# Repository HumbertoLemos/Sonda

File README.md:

# Sonda
Projeto da sonda para ensaios em aeronaves

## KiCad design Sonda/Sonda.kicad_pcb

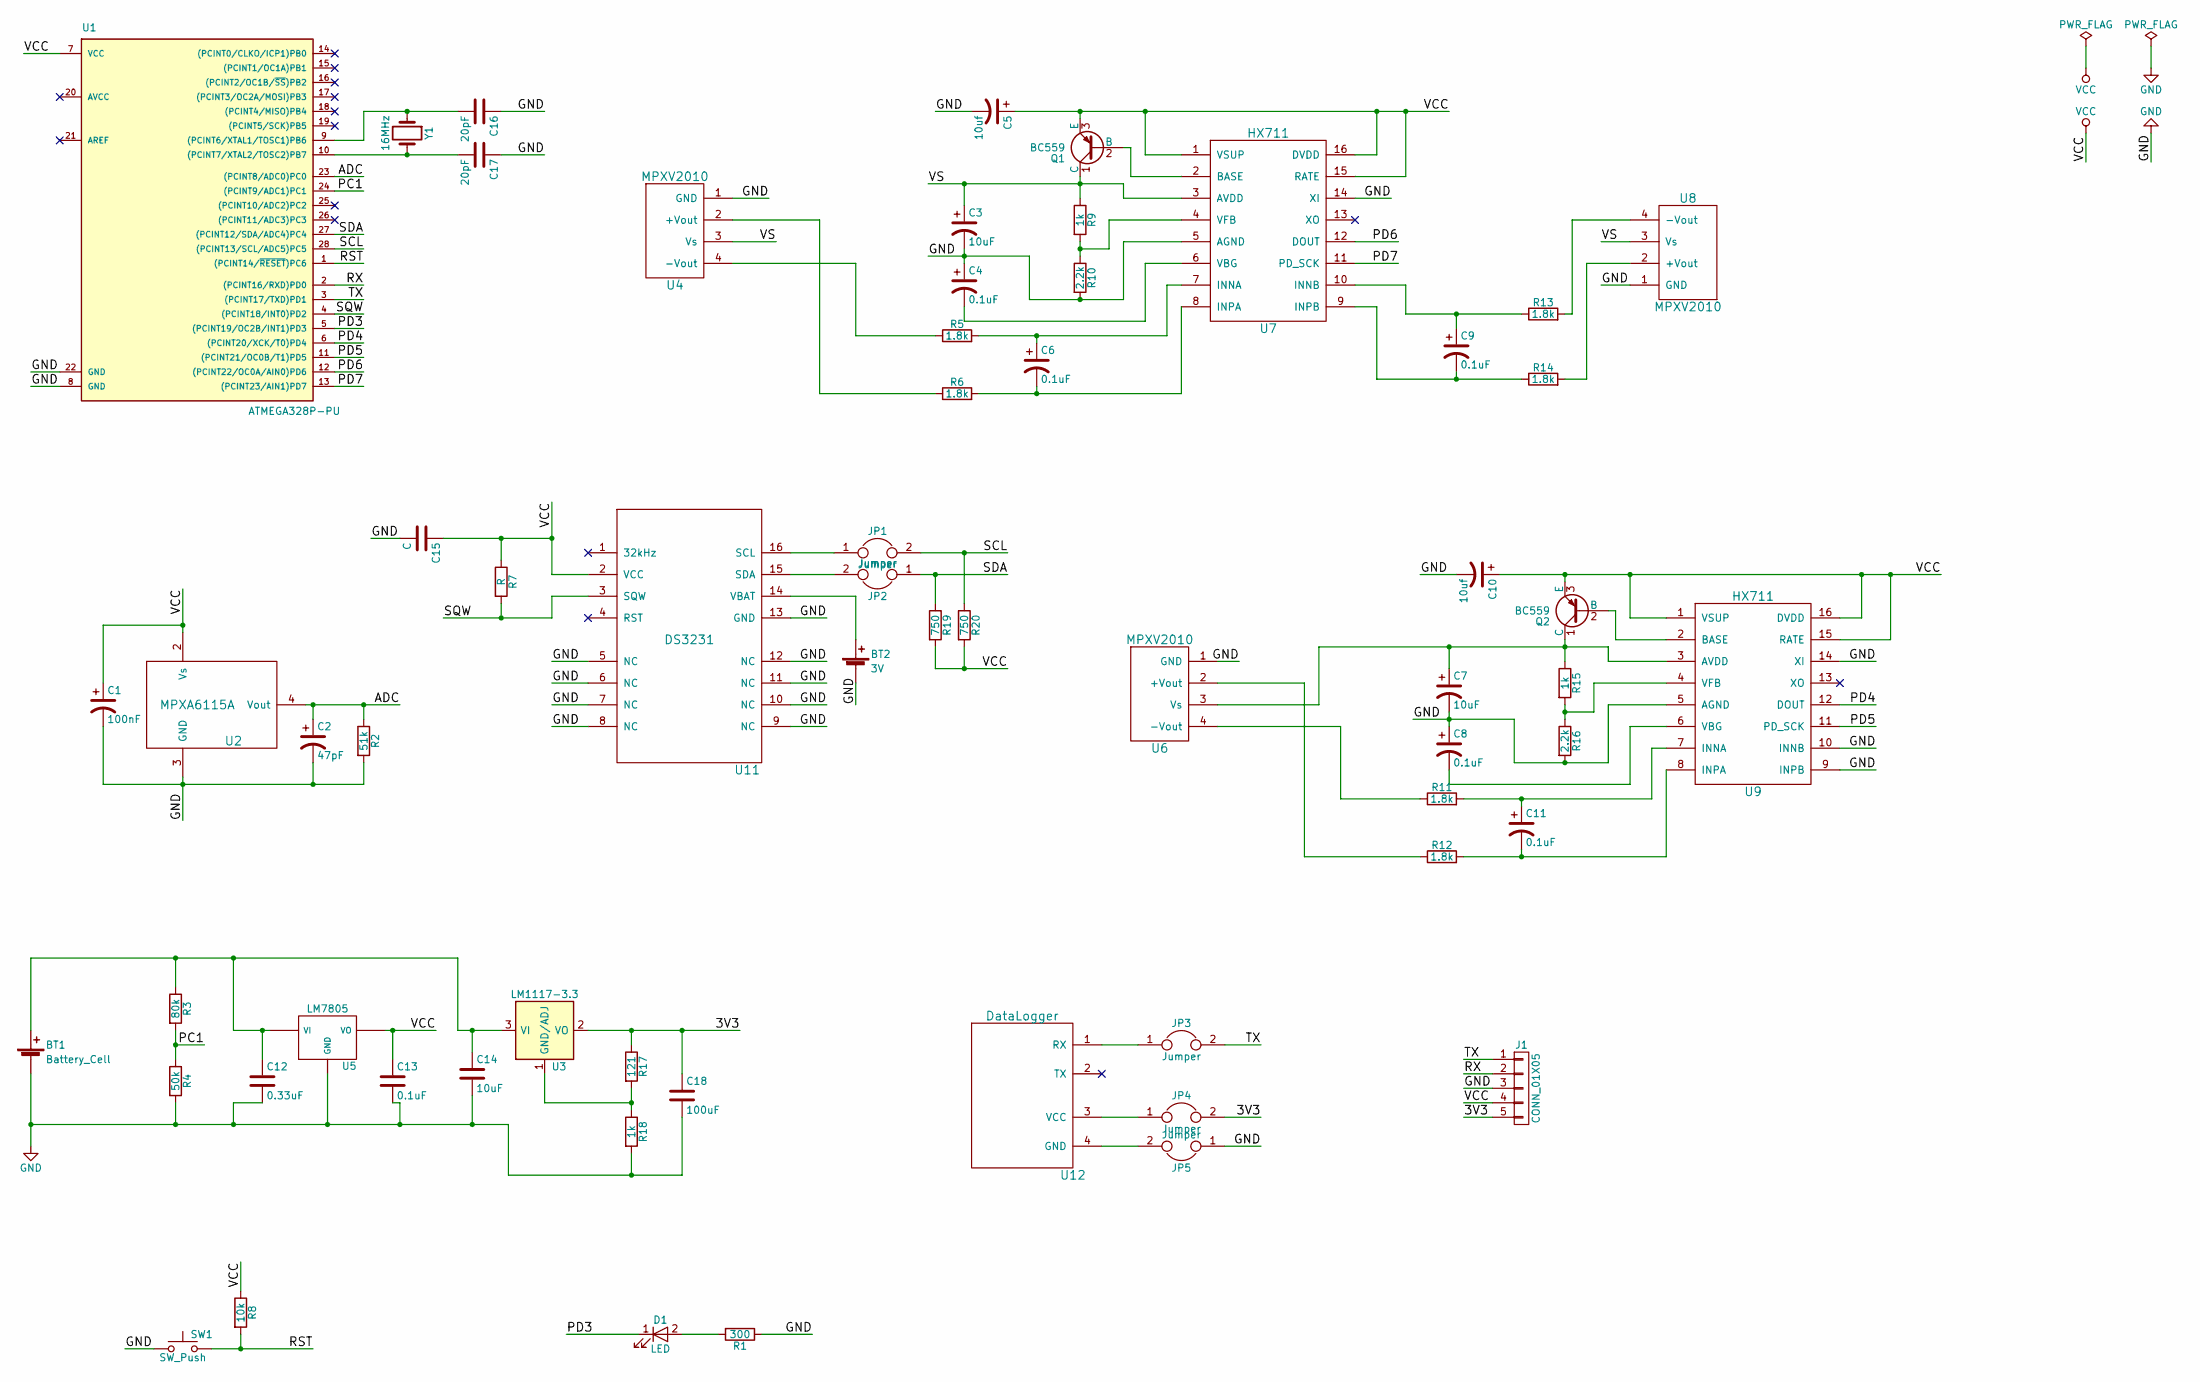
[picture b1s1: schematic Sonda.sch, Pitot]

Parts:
BT1: Battery_Cell; Pin_Header_Straight_1x02_Pitch2.54mm
BT2: 3V; SuporteBateria
C1: 100nF; C_Disc_D4.3mm_W1.9mm_P5.00mm
C2: 47pF; C_Disc_D4.3mm_W1.9mm_P5.00mm
C3, C7, C14: 10uF; C_Disc_D4.3mm_W1.9mm_P5.00mm
C4, C6, C8, C9, C11, C13: 0.1uF; C_Disc_D4.3mm_W1.9mm_P5.00mm
C5, C10: 10uf; C_Disc_D4.3mm_W1.9mm_P5.00mm
C12: 0.33uF; C_Disc_D4.3mm_W1.9mm_P5.00mm
C15: C; C_Disc_D4.3mm_W1.9mm_P5.00mm
C16, C17: 20pF; C_Disc_D4.3mm_W1.9mm_P5.00mm
C18: 100uF; C_Disc_D4.3mm_W1.9mm_P5.00mm
D1: LED; LED_D3.0mm
J1: CONN_01X05; Pin_Header_Straight_1x05_Pitch2.54mm
JP1, JP2, JP3, JP4, JP5: Jumper; Pin_Header_Straight_1x02_Pitch2.54mm
Q1, Q2: BC559; TO-92_Molded_Narrow
R1: 300; R_Axial_DIN0207_L6.3mm_D2.5mm_P10.16mm_Horizontal
R2: 51k; R_Axial_DIN0207_L6.3mm_D2.5mm_P10.16mm_Horizontal
R3: 80k; R_Axial_DIN0207_L6.3mm_D2.5mm_P10.16mm_Horizontal
R4: 50k; R_Axial_DIN0207_L6.3mm_D2.5mm_P10.16mm_Horizontal
R5, R6, R11, R12, R13, R14: 1.8k; R_Axial_DIN0207_L6.3mm_D2.5mm_P10.16mm_Horizontal
R7: R; R_Axial_DIN0207_L6.3mm_D2.5mm_P10.16mm_Horizontal
R8: 10k; R_Axial_DIN0207_L6.3mm_D2.5mm_P10.16mm_Horizontal
R9, R15, R18: 1k; R_Axial_DIN0207_L6.3mm_D2.5mm_P10.16mm_Horizontal
R10, R16: 2.2k; R_Axial_DIN0207_L6.3mm_D2.5mm_P10.16mm_Horizontal
R17: 121; R_Axial_DIN0207_L6.3mm_D2.5mm_P10.16mm_Horizontal
R19, R20: 750; R_Axial_DIN0207_L6.3mm_D2.5mm_P10.16mm_Horizontal
SW1: SW_Push; SW_PUSH_6mm
U1: ATMEGA328P-PU; DIP-28_W7.62mm_Socket_LongPads
U2: MPXA6115A; MPXH6115A
U3: LM1117-3.3; TO-220_Vertical
U4, U6, U8: MPXV2010; MPXV2010DP
U5: LM7805; TO-220_Vertical
U7, U9: HX711; SOP-16_4.4x10.4mm_Pitch1.27mm
U11: DS3231; SOIC-16W_7.5x10.3mm_Pitch1.27mm
U12: DataLogger; OpenLog
Y1: 16MHz; Crystal_HC49-U_Vertical

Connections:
/3V3: C18.1, J1.5, JP4.2, R17.1, U3.2 (VO), U3.4 (VO)
/ADC: C2.1, R2.1, U1.23 ((PCINT8/ADC0)PC0), U2.4 (Vout)
/PC1: R3.2, R4.1, U1.24 ((PCINT9/ADC1)PC1)
/PD3: D1.1 (K), U1.5 ((PCINT19/OC2B/INT1)PD3)
/PD4: U1.6 ((PCINT20/XCK/T0)PD4), U9.12 (DOUT)
/PD5: U1.11 ((PCINT21/OC0B/T1)PD5), U9.11 (PD_SCK)
/PD6: U1.12 ((PCINT22/OC0A/AIN0)PD6), U7.12 (DOUT)
/PD7: U1.13 ((PCINT23/AIN1)PD7), U7.11 (PD_SCK)
/RST: R8.2, SW1.2, U1.1 ((PCINT14/~RESET~)PC6)
/RX: J1.2, U1.2 ((PCINT16/RXD)PD0)
/SCL: JP1.2, R20.1, U1.28 ((PCINT13/SCL/ADC5)PC5)
/SDA: JP2.1, R19.1, U1.27 ((PCINT12/SDA/ADC4)PC4)
/SQW: R7.2, U1.4 ((PCINT18/INT0)PD2), U11.3 (SQW)
/TX: J1.1, JP3.2, U1.3 ((PCINT17/TXD)PD1)
/VS: C3.1, Q1.1 (C), R9.1, U4.3 (Vs), U7.3 (AVDD), U8.3 (Vs)
GND: BT1.2 (-), BT2.2 (-), C1.2, C2.2, C3.2, C4.1, C5.2, C7.2, C8.1, C10.2, C12.2, C13.2, C14.2, C15.2, C16.1, C17.1, C18.2, J1.3, JP5.1, R1.1, R2.2, R4.2, R10.2, R16.2, R18.2, SW1.1, U1.8 (GND), U1.22 (GND), U2.3 (GND), U4.1 (GND), U5.GND, U6.1 (GND), U7.5 (AGND), U7.14 (XI), U8.1 (GND), U9.5 (AGND), U9.9 (INPB), U9.10 (INNB), U9.14 (XI), U11.5 (NC), U11.6 (NC), U11.7 (NC), U11.8 (NC), U11.9 (NC), U11.10 (NC), U11.11 (NC), U11.12 (NC), U11.13 (GND)
unnamed: BT1.1 (+), C12.1, C14.1, R3.1, U3.3 (VI), U5.VI
unnamed: BT2.1 (+), U11.14 (VBAT)
unnamed: C4.2, U7.6 (VBG)
unnamed: C6.1, R5.2, U7.7 (INNA)
unnamed: C6.2, R6.2, U7.8 (INPA)
unnamed: C7.1, Q2.1 (C), R15.1, U6.3 (Vs), U9.3 (AVDD)
unnamed: C8.2, U9.6 (VBG)
unnamed: C9.1, R13.1, U7.10 (INNB)
unnamed: C9.2, R14.1, U7.9 (INPB)
unnamed: C11.1, R11.2, U9.7 (INNA)
unnamed: C11.2, R12.2, U9.8 (INPA)
unnamed: C16.2, U1.9 ((PCINT6/XTAL1/TOSC1)PB6), Y1.1
unnamed: C17.2, U1.10 ((PCINT7/XTAL2/TOSC2)PB7), Y1.2
unnamed: D1.2 (A), R1.2
unnamed: JP1.1, U11.16 (SCL)
unnamed: JP2.2, U11.15 (SDA)
unnamed: JP3.1, U12.1 (RX)
unnamed: JP4.1, U12.3 (VCC)
unnamed: JP5.2, U12.4 (GND)
unnamed: Q1.2 (B), U7.2 (BASE)
unnamed: Q2.2 (B), U9.2 (BASE)
unnamed: R5.1, U4.4 (-Vout)
unnamed: R6.1, U4.2 (+Vout)
unnamed: R9.2, R10.1, U7.4 (VFB)
unnamed: R11.1, U6.4 (-Vout)
unnamed: R12.1, U6.2 (+Vout)
unnamed: R13.2, U8.4 (-Vout)
unnamed: R14.2, U8.2 (+Vout)
unnamed: R15.2, R16.1, U9.4 (VFB)
unnamed: R17.2, R18.1, U3.1 (GND/ADJ)
VCC: C1.1, C5.1, C10.1, C13.1, C15.1, J1.4, Q1.3 (E), Q2.3 (E), R7.1, R8.1, R19.2, R20.2, U1.7 (VCC), U2.2 (Vs), U5.VO, U7.1 (VSUP), U7.15 (RATE), U7.16 (DVDD), U9.1 (VSUP), U9.15 (RATE), U9.16 (DVDD), U11.2 (VCC)

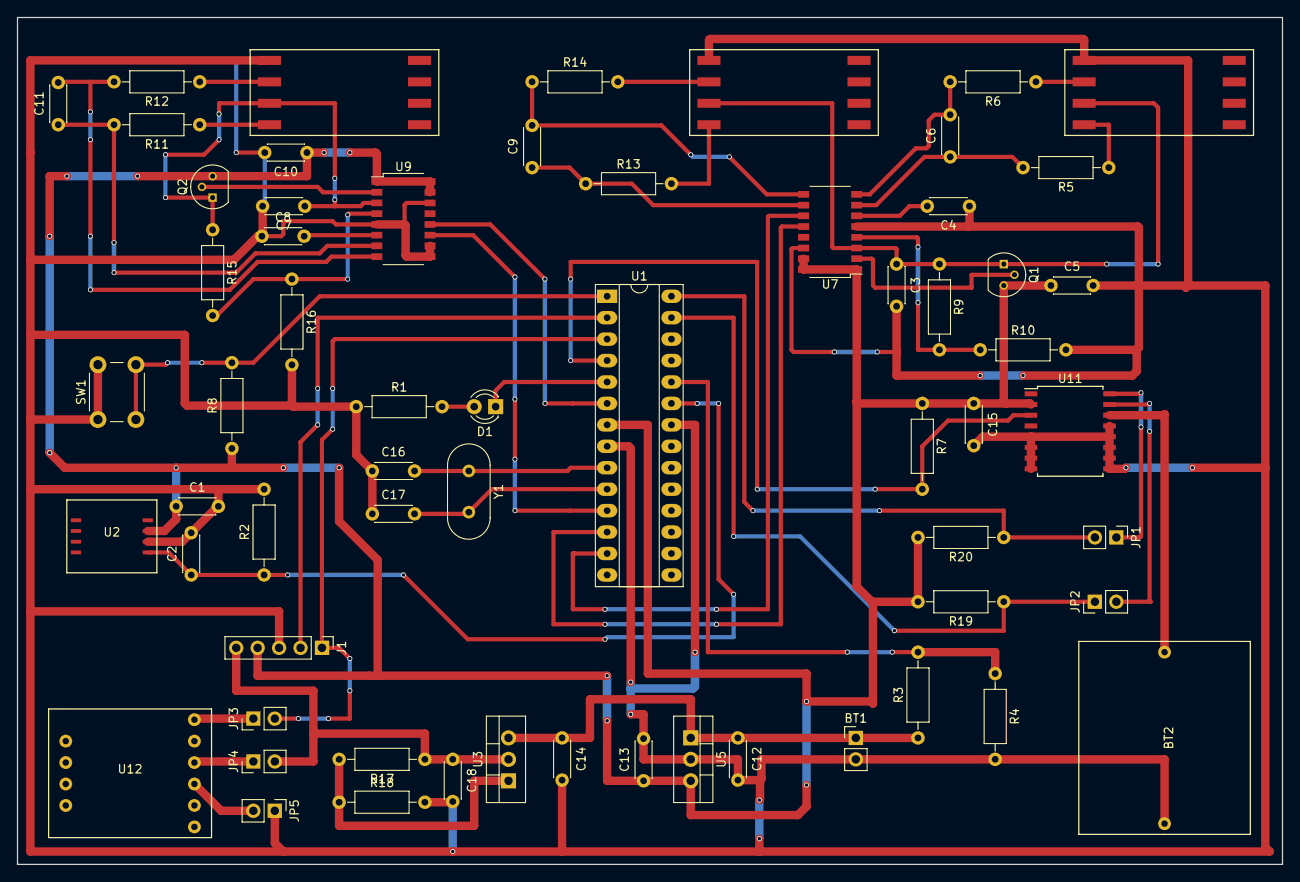
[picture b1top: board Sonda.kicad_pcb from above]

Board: 2 copper layers, 149.9 x 100.3 mm, 62 parts (0 on the bottom side), 47 nets.

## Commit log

2017-08-07 modificacoes no circuito, pcb
2017-08-23 PCB feito
2017-08-31 PCB changes
